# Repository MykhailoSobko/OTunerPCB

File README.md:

# OTunerPCB
Schematics and PCB for the OTuner - optical guitar tuner, which uses stroboscopic effect instead of sound.

The project was done as a part of Principles of Computer Organization course at UCU in association with mentors from Renesas company.

The ```main``` branch contains files that ended up as a final version for the student project and the ```dev``` branch contains files for future development as a standalone project.

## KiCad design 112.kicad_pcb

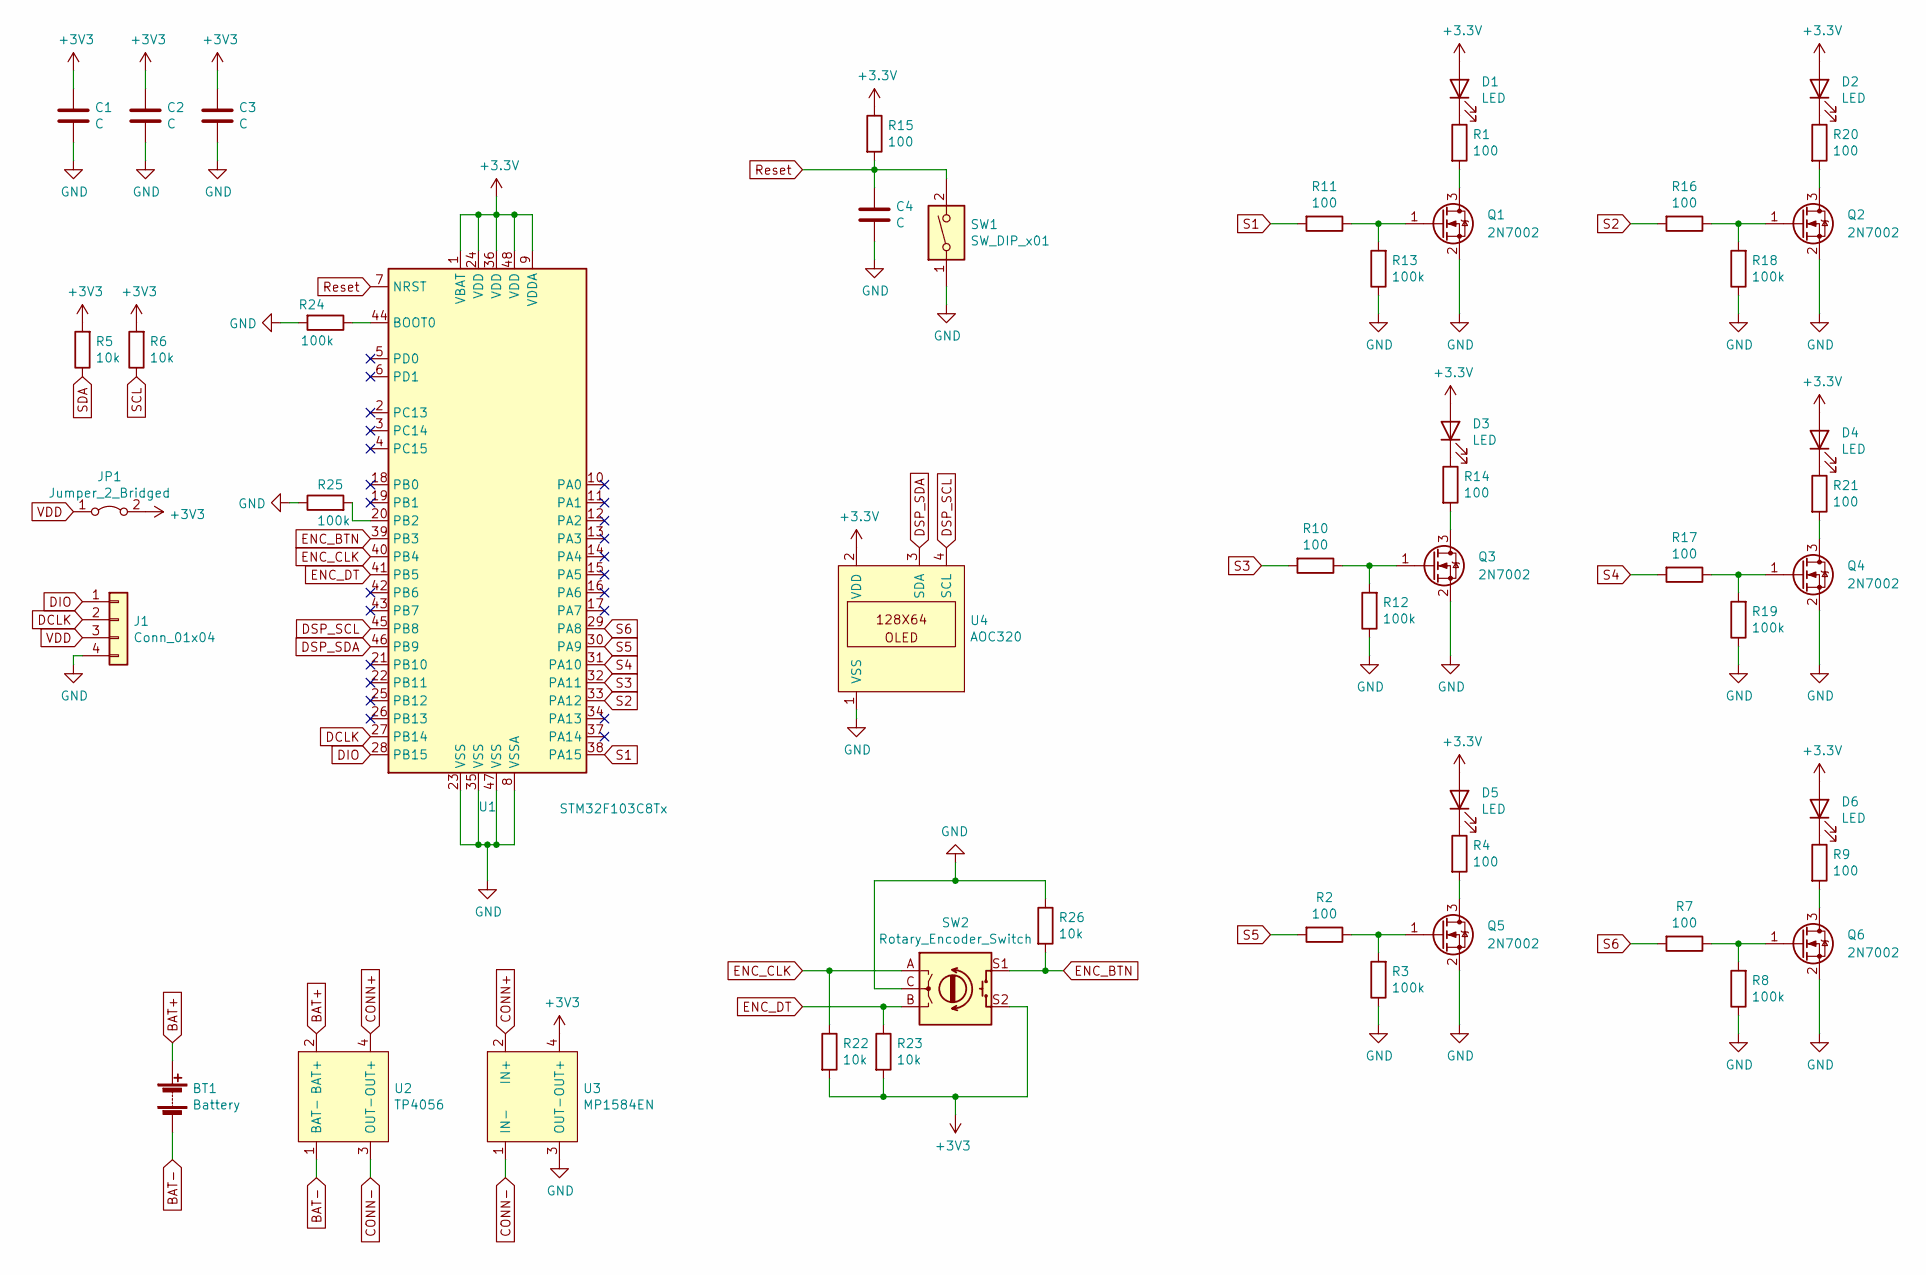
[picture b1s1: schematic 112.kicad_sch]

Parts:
BT1: Battery; RAC163
C1, C2, C3, C4: C; C_0805_2012Metric
D1, D2, D3, D4, D5, D6: LED; LED_0805_2012Metric_Pad1.15x1.40mm_HandSolder
J1: Conn_01x04; PinSocket_1x04_P2.54mm_Vertical
JP1: Jumper_2_Bridged; PinHeader_1x02_P2.54mm_Vertical
Q1, Q2, Q3, Q4, Q5, Q6: 2N7002; SOT-23
R1, R2, R4, R7, R9, R10, R11, R14, R15, R16, R17, R20, R21: 100; R_0805_2012Metric_Pad1.20x1.40mm_HandSolder
R3, R8, R12, R13, R18, R19, R24, R25: 100k; R_0805_2012Metric_Pad1.20x1.40mm_HandSolder
R5, R6, R22, R23, R26: 10k; R_0805_2012Metric_Pad1.20x1.40mm_HandSolder
SW1: SW_DIP_x01; SW_DIP_SPSTx01_Slide_6.7x4.1mm_W6.73mm_P2.54mm_LowProfile_J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
SW2: Rotary_Encoder_Switch; EC1102S-4A-F1
U1: STM32F103C8Tx; LQFP-48_7x7mm_P0.5mm
U2: TP4056
U3: MP1584EN
U4: AOC320

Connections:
BAT+: BT1.1 (+), U2.2 (BAT+)
BAT-: BT1.2 (-), U2.1 (BAT-)
CONN+: U2.4 (OUT+), U3.2 (IN+)
CONN-: U2.3 (OUT-), U3.1 (IN-)
DCLK: J1.2, U1.27 (PB14)
DIO: J1.1, U1.28 (PB15)
DSP_SCL: U1.45 (PB8), U4.4 (SCL)
DSP_SDA: U1.46 (PB9), U4.3 (SDA)
ENC_BTN: R26.2, SW2.S1, U1.39 (PB3)
ENC_CLK: R22.1, SW2.A, U1.40 (PB4)
ENC_DT: R23.1, SW2.B, U1.41 (PB5)
GND: C1.2, C2.2, C3.2, C4.2, J1.4, Q1.2 (S), Q2.2 (S), Q3.2 (S), Q4.2 (S), Q5.2 (S), Q6.2 (S), R3.1, R8.1, R12.1, R13.1, R18.1, R19.1, R24.2, R25.1, R26.1, SW1.1, SW2.C, U1.8 (VSSA), U1.23 (VSS), U1.35 (VSS), U1.47 (VSS), U3.3 (OUT-), U4.1 (VSS)
unnamed: D1.1 (K), R1.1
unnamed: D2.1 (K), R20.1
unnamed: D3.1 (K), R14.1
unnamed: D4.1 (K), R21.1
unnamed: D5.1 (K), R4.1
unnamed: D6.1 (K), R9.1
unnamed: Q1.1 (G), R11.1, R13.2
unnamed: Q1.3 (D), R1.2
unnamed: Q2.1 (G), R16.1, R18.2
unnamed: Q2.3 (D), R20.2
unnamed: Q3.1 (G), R10.1, R12.2
unnamed: Q3.3 (D), R14.2
unnamed: Q4.1 (G), R17.1, R19.2
unnamed: Q4.3 (D), R21.2
unnamed: Q5.1 (G), R2.1, R3.2
unnamed: Q5.3 (D), R4.2
unnamed: Q6.1 (G), R7.1, R8.2
unnamed: Q6.3 (D), R9.2
unnamed: R24.1, U1.44 (BOOT0)
unnamed: R25.2, U1.20 (PB2)
Reset: C4.1, R15.2, SW1.2, U1.7 (NRST)
S1: R11.2, U1.38 (PA15)
S2: R16.2, U1.33 (PA12)
S3: R10.2, U1.32 (PA11)
S4: R17.2, U1.31 (PA10)
S5: R2.2, U1.30 (PA9)
S6: R7.2, U1.29 (PA8)
SCL: R6.1
SDA: R5.1
VDD: J1.3, JP1.1 (A)

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
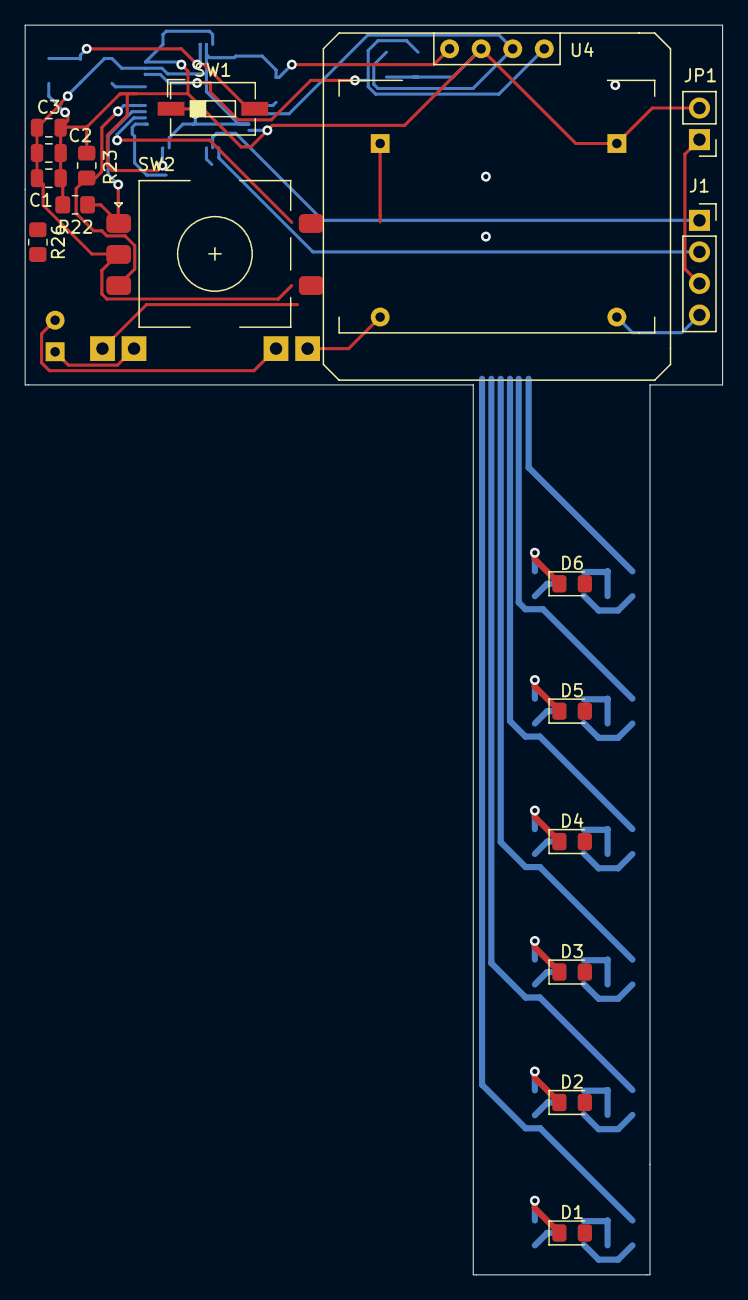
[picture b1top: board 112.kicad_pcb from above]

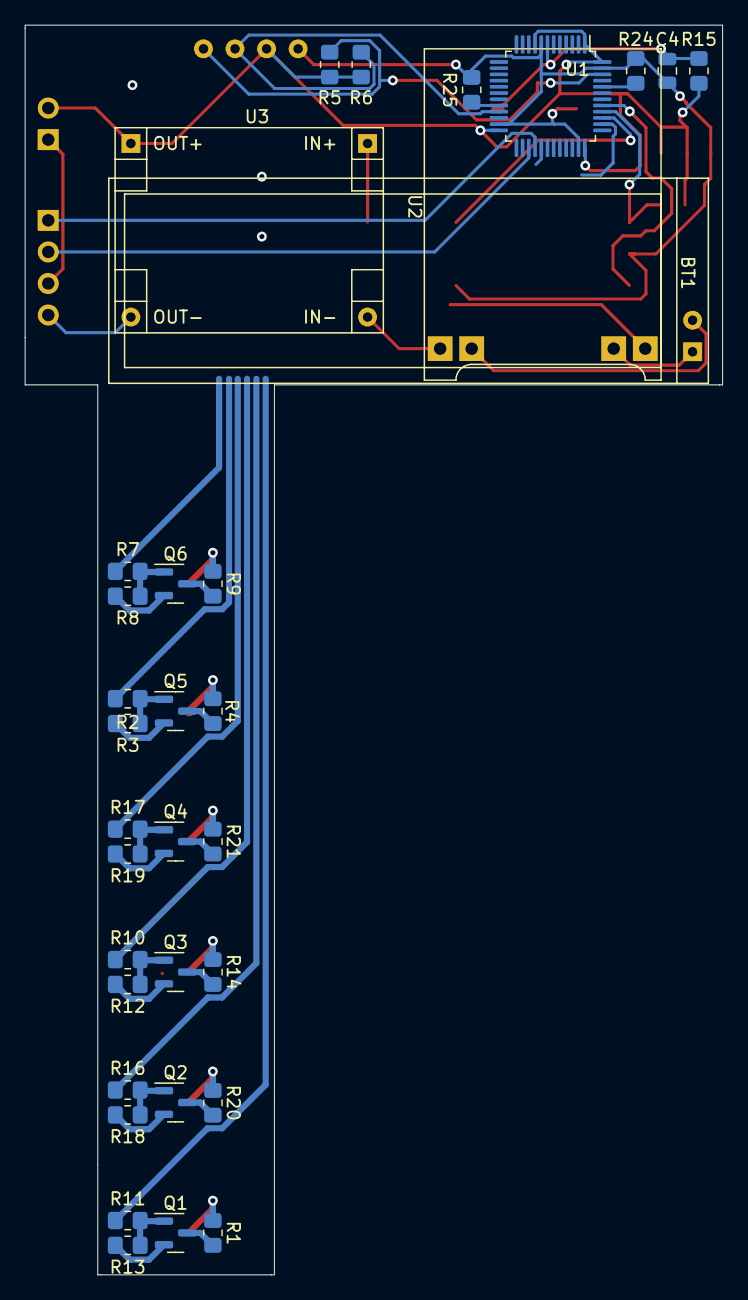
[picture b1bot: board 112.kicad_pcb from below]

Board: 2 copper layers, 56.1 x 100.6 mm, 51 parts (34 on the bottom side), 41 nets.

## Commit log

2022-01-14 Add files for the release version
2022-01-14 Add missing library files
2022-01-14 Add the work-in-progress version for future releases
2022-01-14 Update PCB layout
2022-01-14 Add images
